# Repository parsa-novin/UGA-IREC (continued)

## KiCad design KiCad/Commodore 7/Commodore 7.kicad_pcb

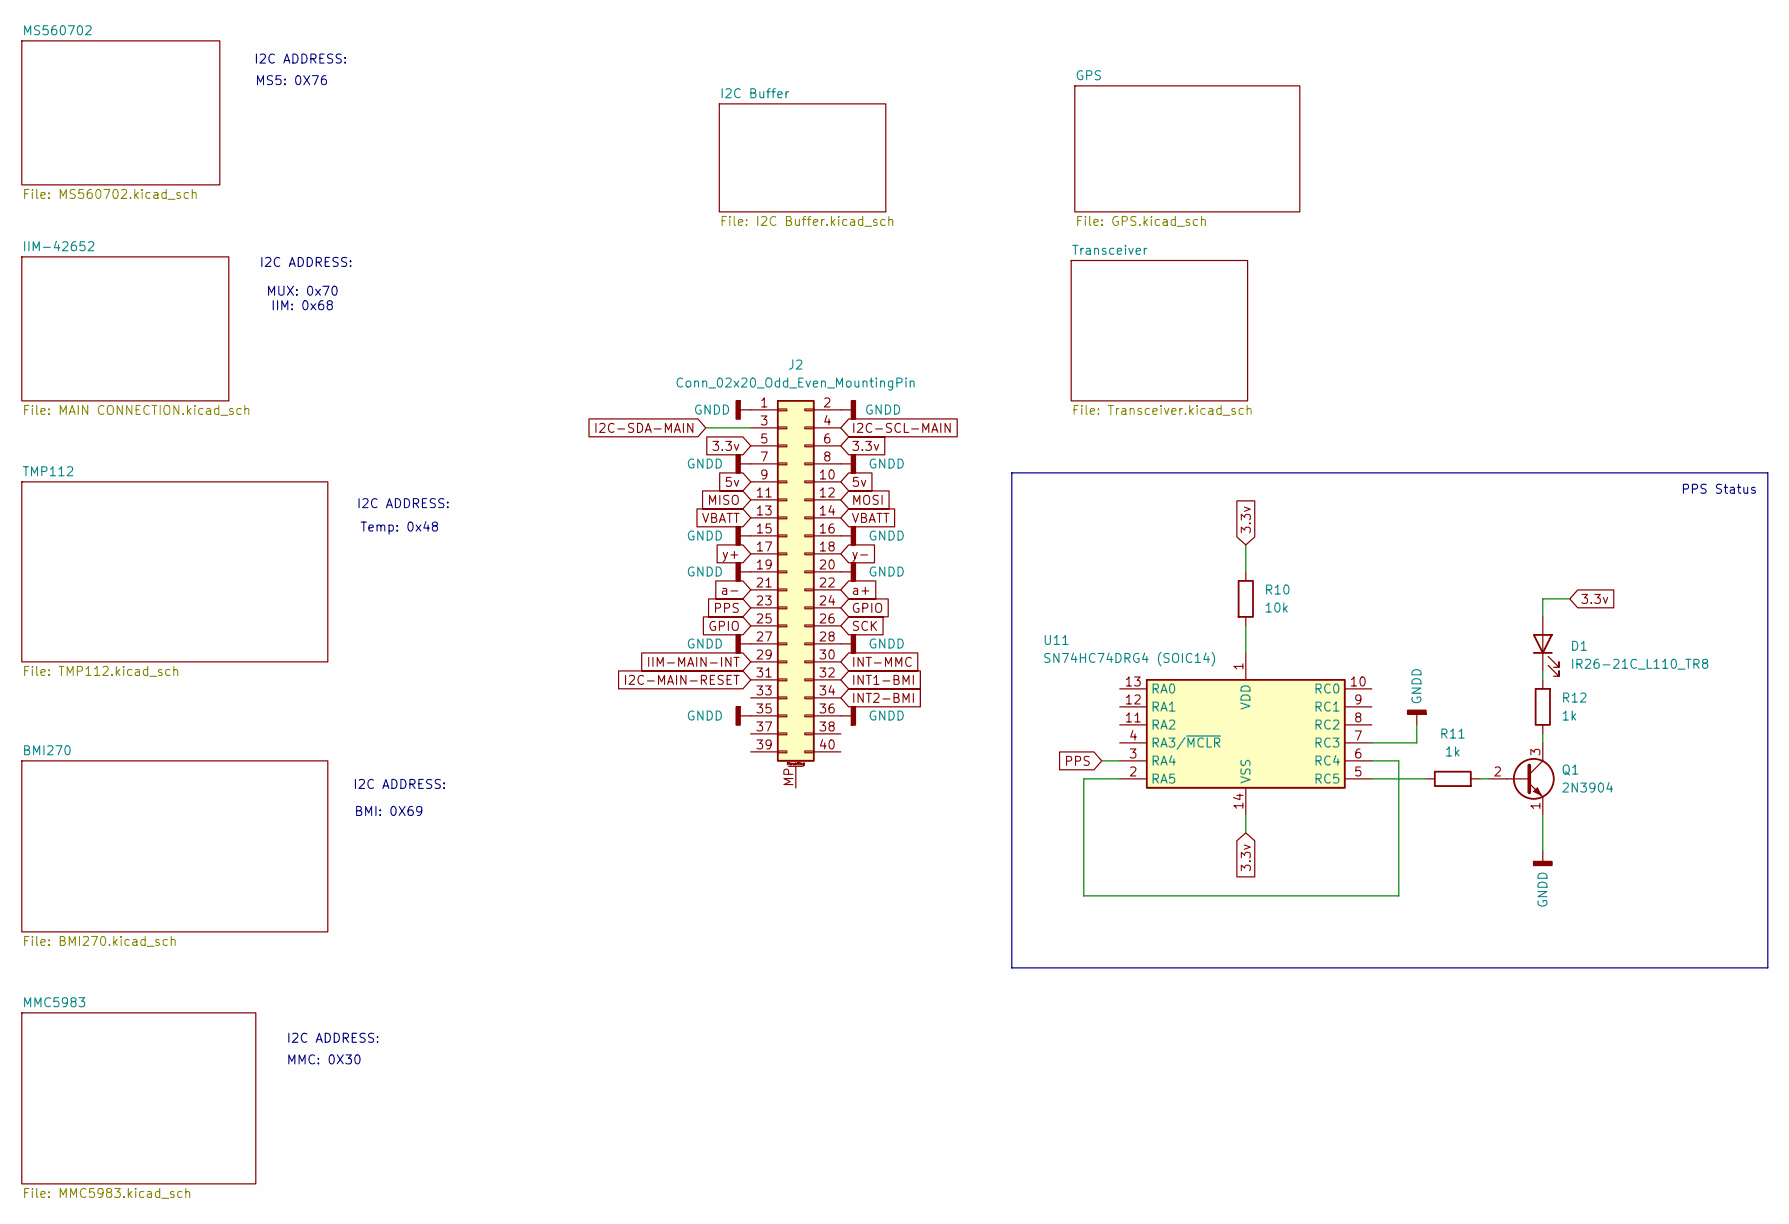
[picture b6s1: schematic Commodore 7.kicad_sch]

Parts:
D1: IR26-21C_L110_TR8; LED_1206_3216Metric
J2: Conn_02x20_Odd_Even_MountingPin; PinHeader_2x20_P2.54mm_Vertical
Q1: 2N3904; TO-92_Inline
R10: 10k; R_1206_3216Metric
R11, R12: 1k; R_1206_3216Metric
U11: SN74HC74DRG4 (SOIC14); SOIC-14_3.9x8.7mm_P1.27mm

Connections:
3.3v: D1.2 (A), J2.5, J2.6, R10.1, U11.14 (VSS); also elsewhere on the board
5v: J2.9, J2.10
GNDD: J2.1, J2.2, J2.7, J2.8, J2.15, J2.16, J2.19, J2.20, J2.27, J2.28, J2.35, J2.36, Q1.1 (E), U11.7 (RC3); also elsewhere on the board
GPIO: J2.24, J2.25; also elsewhere on the board
I2C-MAIN-RESET: J2.31; also elsewhere on the board
I2C-SCL-MAIN: J2.4; also elsewhere on the board
I2C-SDA-MAIN: J2.3; also elsewhere on the board
IIM-MAIN-INT: J2.29; also elsewhere on the board
INT1-BMI: J2.32; also elsewhere on the board
INT2-BMI: J2.34; also elsewhere on the board
INT-MMC: J2.30; also elsewhere on the board
MISO: J2.11
MOSI: J2.12
unnamed: D1.1 (K), R12.2
unnamed: Q1.2 (B), R11.2
unnamed: Q1.3 (C), R12.1
unnamed: U11.2 (RA5), U11.6 (RC4)
unnamed: R11.1, U11.5 (RC5)
unnamed: R10.2, U11.1 (VDD)
PPS: J2.23, U11.3 (RA4); also elsewhere on the board
SCK: J2.26
VBATT: J2.13, J2.14
a+: J2.22; also elsewhere on the board
a-: J2.21; also elsewhere on the board
y+: J2.17; also elsewhere on the board
y-: J2.18; also elsewhere on the board

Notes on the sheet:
I2C ADDRESS:
PPS Status
MUX: 0x70 IIM: 0x68
BMI: 0X69
I2C ADDRESS:
MMC: 0X30
MS5: 0X76
Temp: 0x48

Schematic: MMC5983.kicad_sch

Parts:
C4: 10uF; CAP_CC0805_YAG
C5: 1uF; YAG_CC0603_YAG
U4: MMC5983MA-Magnetomer; PQFN50P300X300X100-16N; PARTREV A

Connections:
3.3v: C5.1, U4.2 (VDD), U4.4 (~SPI_CS), U4.13 (VDDIO); also elsewhere on the board
GNDD: C4.2, C5.2, U4.9 (GND), U4.11 (GND__1); also elsewhere on the board
I2C-SCL-MAIN: U4.1 (SCL/SPI_SCK); also elsewhere on the board
I2C-SDA-MAIN: U4.16 (SDA/SPI_SDI); also elsewhere on the board
INT-MMC: U4.15 (INT); also elsewhere on the board
unnamed: C4.1, U4.10 (CAP)

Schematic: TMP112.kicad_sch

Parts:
C1: 10nF; CAPC17595_87N_KEM
U1: TMP112AIDRLR-Temperature; SOT50P160X60-6N

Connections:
GNDD: C1.2, U1.2 (GND), U1.3 (ALERT), U1.4 (ADD0); also elsewhere on the board
I2C-SCL-MAIN: U1.1 (SCL); also elsewhere on the board
I2C-SDA-MAIN: U1.6 (SDA); also elsewhere on the board
unnamed: C1.1, U1.5 (V+)

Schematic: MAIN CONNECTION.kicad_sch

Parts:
C12, C13: 2.2uf; CAP_CC0805_YAG
C14, C15: .1uf; CC0603N_YAG
C16, C17: 10nF; CAPC17595_87N_KEM
R1, R2, R3, R4: 4.7k; YAG_R0402_YAG
R19, R20, R21, R23, R27, R28: 2.7K; RES0805_CRG_TYCO_TYC
U8: IIM-42652 - Main Accelerometer 2; Bosch_LGA-14_3x2.5mm_P0.5mm
U9: IIM-42652 Main Accelerometer; Bosch_LGA-14_3x2.5mm_P0.5mm
U10: TCA9543APWR; SOP65P640X120-14N

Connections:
3.3v: C12.1, C13.1, C14.1, C15.1, C16.1, C17.1, R1.2, R2.2, R3.2, R4.2, R19.2, R20.2, R21.2, R23.2, R27.2, R28.2, U8.5 (VDDIO), U8.8 (VDD), U8.12 (AP_CS), U9.5 (VDDIO), U9.8 (VDD), U9.12 (AP_CS), U10.14 (VCC); also elsewhere on the board
GNDD: C12.2, C13.2, C14.2, C15.2, C16.2, C17.2, U8.1 (AP_SDO/AP_AD0), U8.6 (GND), U8.7 (GND), U8.9 (INT2/FSYNC/CLKIN), U9.1 (AP_SDO/AP_AD0), U9.6 (GND), U9.7 (GND), U9.9 (INT2/FSYNC/CLKIN), U10.1 (AO), U10.2 (A1), U10.7 (GND); also elsewhere on the board
I2C-MAIN-RESET: R3.1, U10.3 (RESET); also elsewhere on the board
I2C-SCL-MAIN: R2.1, U10.12 (SCL); also elsewhere on the board
I2C-SDA-MAIN: R1.1, U10.13 (SDA); also elsewhere on the board
IIM-MAIN-INT: R4.1, U10.11 (INT); also elsewhere on the board
INT-IIM1: R27.1, U9.4 (INT1/INT), U10.4 (INTO)
INT-IIM2: R28.1, U8.4 (INT1/INT), U10.8 (INT1)
SCL-IIM1: R20.1, U9.13 (AP_SCL/AP_SCLK), U10.6 (SCO)
SCL-IIM2: R19.1, U8.13 (AP_SCL/AP_SCLK), U10.10 (8C1)
SDA-IIM1: R21.1, U9.14 (AP_SDA/AP_SDIO/AP_SDI), U10.5 (SDO)
SDA-IIM2: R23.1, U8.14 (AP_SDA/AP_SDIO/AP_SDI), U10.9 (SD1)

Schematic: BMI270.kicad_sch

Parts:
C2, C3: .1uF; CC0603N_YAG
R6: 2.7K; RES0805_CRG_TYCO_TYC
R8: 2.7K; R_1206_3216Metric
U3: BMI270 - Secondary Accelerometer; XDCR_BMI270

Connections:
3.3v: C2.1, C3.1, R6.1, R8.1, U3.5 (VDDIO), U3.8 (VDD); also elsewhere on the board
GNDD: C2.2, C3.2, U3.6 (GNDIO), U3.7 (GND), U3.10 (OSCB), U3.11 (OSDO); also elsewhere on the board
I2C-SCL-MAIN: U3.13 (SCX); also elsewhere on the board
I2C-SDA-MAIN: U3.14 (SDX); also elsewhere on the board
INT1-BMI: U3.4 (INT1); also elsewhere on the board
INT2-BMI: U3.9 (INT2); also elsewhere on the board
unnamed: R8.2, U3.12 (CSB)
unnamed: R6.2, U3.1 (SDO)

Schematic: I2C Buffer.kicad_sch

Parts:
R9: RC0402FR-0710KL; YAG_R0402_YAG; PARTREV V.12
U6: TCA9509DGKR; DGK8

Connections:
3.3v: R9.2, U6.1 (VCCA), U6.8 (VCCB); also elsewhere on the board
GNDD: U6.4 (GND); also elsewhere on the board
I2C-SCL-MAIN: U6.2 (SCLA), U6.7 (SCLB); also elsewhere on the board
I2C-SDA-MAIN: U6.3 (SDAA), U6.6 (SDAB); also elsewhere on the board
unnamed: R9.1, U6.5 (EN)

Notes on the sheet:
Connect at diffrent points

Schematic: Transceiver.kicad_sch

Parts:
R5, R7: RC1206FR-0724RL; R_1206_3216Metric
U7: SN65HVD74DR; D8_TEX

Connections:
3.3v: U7.1 (VCC); also elsewhere on the board
GNDD: U7.4 (GND); also elsewhere on the board
R: U7.2 (R); also elsewhere on the board
T: U7.3 (D); also elsewhere on the board
a+: R5.1, U7.8 (A); also elsewhere on the board
a-: R5.2, U7.7 (B); also elsewhere on the board
y+: R7.1, U7.5 (Y); also elsewhere on the board
y-: R7.2, U7.6 (Z); also elsewhere on the board

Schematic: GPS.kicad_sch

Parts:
E1: YG0043AA; XDCR_YG0043AA; PARTREV 1.3
IC1: BGU7004,115; BGU7004115; Manufacturer_Part_Number BGU7004,115; Mouser Part Number 771-BGU7004,115
IC2: LD56020M180R; SOT-23-5; Manufacturer_Part_Number LD56020M180R
L1: 5.6nH; INDC1006X60N
U2: NEO-M9N-00B; XCVR_NEO-M9N-00B; PARTREV R05
U12: RSF-1575.420-24000-3030-TR

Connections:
3.3v: IC2.1 (VIN), IC2.3 (EN), U2.2 (D_SEL), U2.23 (VCC); also elsewhere on the board
GNDD: IC1.1 (GND_1), IC1.2 (GND_2), IC2.2 (GND), U2.10 (GND), U2.12 (GND__1), U2.13 (GND__2), U2.24 (GND__3), U12.1 (gnd), U12.3 (gnd), U12.4 (gnd), U12.6 (gnd); also elsewhere on the board
GPIO: U2.8 (RESET_N); also elsewhere on the board
unnamed: IC1.3 (RF_IN), L1.2
unnamed: IC1.6 (RF_OUT), U2.11 (RF_IN)
unnamed: IC1.4 (VCC), IC2.5 (VOUT)
unnamed: E1.1, U12.2 (2_Rf_in)
unnamed: L1.1, U12.5 (5_Rf_output)
PPS: U2.3 (TIMEPULSE); also elsewhere on the board
R: U2.21 (RXD/SPI_MOSI); also elsewhere on the board
T: U2.20 (TXD/SPI_MISO); also elsewhere on the board

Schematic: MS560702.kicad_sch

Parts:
U5: MS560702BA03-50 - Barometer; SON125P300X500X100-8N

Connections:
3.3v: U5.1 (VDD), U5.2 (PS); also elsewhere on the board
GNDD: U5.3 (GND), U5.4 (~CSB), U5.5 (~CSB__1), U5.6 (SDO); also elsewhere on the board
I2C-SCL-MAIN: U5.8 (SCLK); also elsewhere on the board
I2C-SDA-MAIN: U5.7 (SDI/SDA); also elsewhere on the board

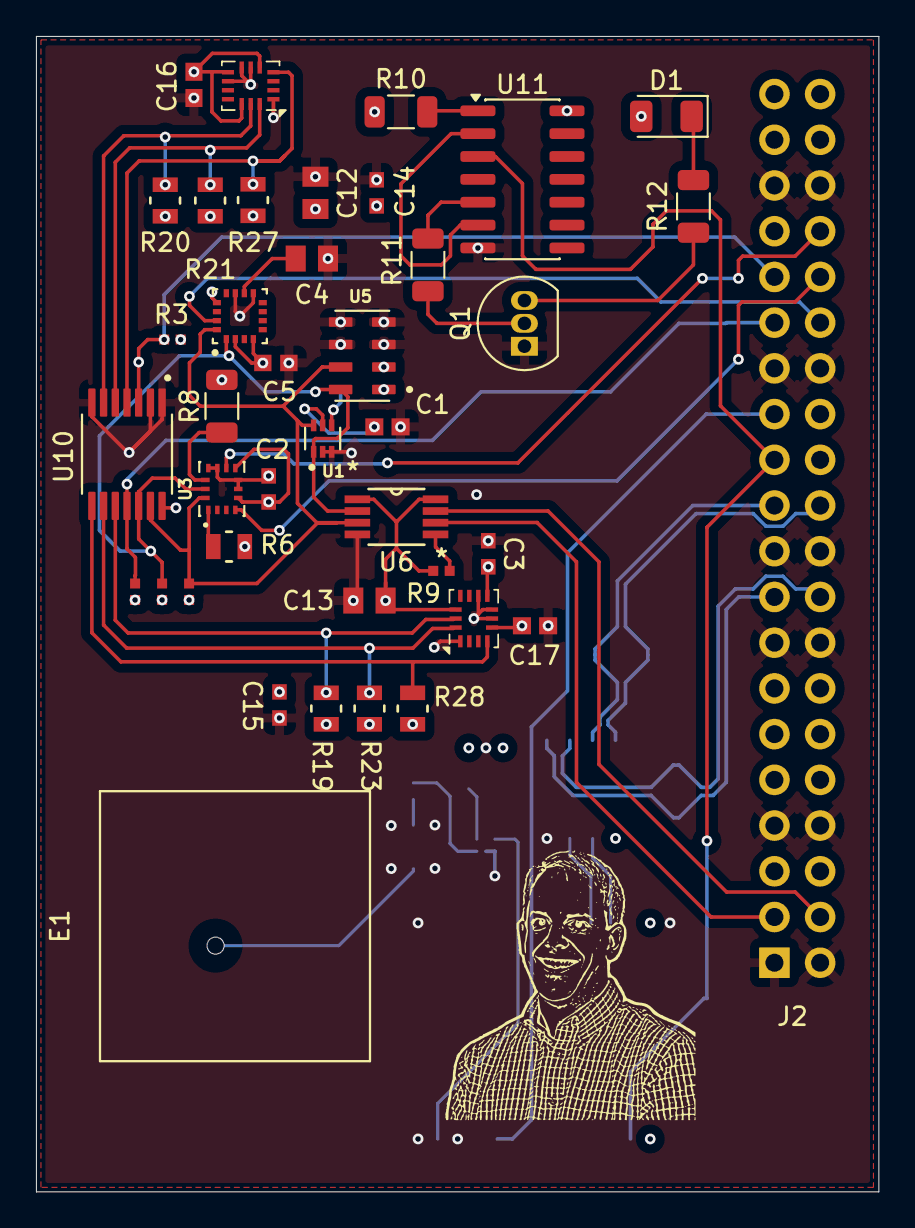
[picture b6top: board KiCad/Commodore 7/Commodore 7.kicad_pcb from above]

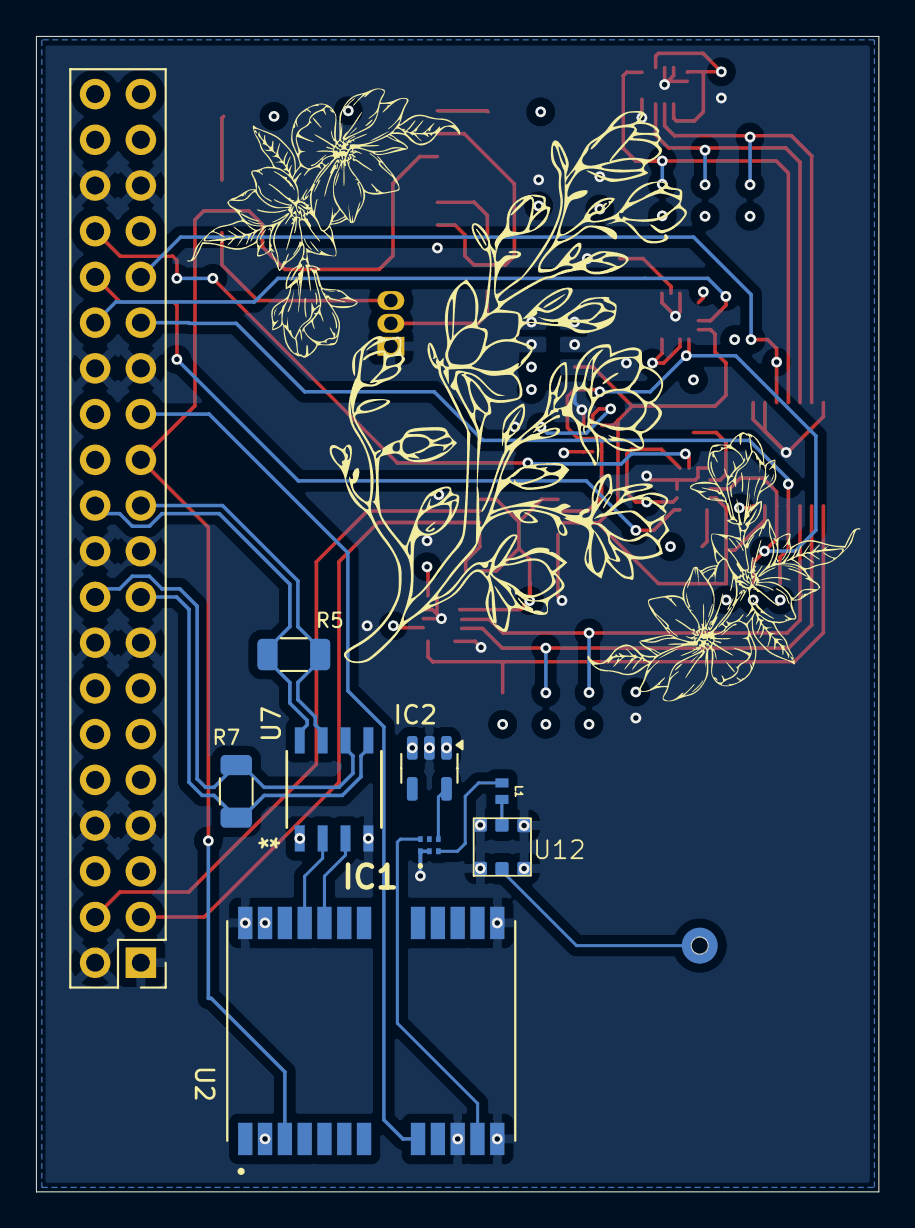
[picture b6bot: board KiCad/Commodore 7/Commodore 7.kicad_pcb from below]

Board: 4 copper layers, 46.8 x 64.2 mm, 48 parts (9 on the bottom side), 41 nets.

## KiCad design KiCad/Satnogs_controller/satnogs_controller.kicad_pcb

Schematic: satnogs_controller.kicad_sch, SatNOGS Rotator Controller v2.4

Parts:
A1, A2: Pololu_Breakout_A4988; Pololu_Breakout-16_15.2x20.3mm
C1, C2, C6, C7, C11, C13: 0.1u; C_0805_2012Metric_Pad1.15x1.40mm_HandSolder
C3, C14, C15: 100u; CP_Elec_6.3x5.3
C4: 100u; CP_Radial_D10.0mm_P5.00mm
C5: 2.2u; C_1210_3225Metric_Pad1.42x2.65mm_HandSolder
C8: 7.5n; C_0805_2012Metric_Pad1.15x1.40mm_HandSolder
C9: 100n; C_0805_2012Metric_Pad1.15x1.40mm_HandSolder
C10: 10p; C_0805_2012Metric_Pad1.15x1.40mm_HandSolder
C12: 47u; C_1210_3225Metric_Pad1.42x2.65mm_HandSolder
D1: D_TVS; D_SMC_Handsoldering
D2, D4: D_Schottky; D_SMC_Handsoldering
D3: D_TVS_x2_AAC; SOT-23_Handsoldering
F1: FUSE; Fuse_1206_3216Metric_Pad1.42x1.75mm_HandSolder
FB1: FILTER - POWER; R_0805_2012Metric_Pad1.15x1.40mm_HandSolder
FB2: FILTER; R_0805_2012Metric_Pad1.15x1.40mm_HandSolder
J1: Conn_01x06_Pin; JST_XA_B06B-XASK-1_1x06_P2.50mm_Vertical
JP1, JP2, JP3, JP4, JP5, JP6, JP7, JP8: Jumper_NO_Small; R_0805_2012Metric_Pad1.15x1.40mm_HandSolder
L1: 27u; L_Bourns_SRR1210A
P1: ISP; PinHeader_2x03_P2.54mm_Vertical
P2: INPUT; PinHeader_2x05_P2.54mm_Vertical
P3: GND-PAD; MountingHole_2.2mm_M2_DIN965_Pad
P4: I2C; PinHeader_2x04_P2.54mm_Vertical
P5: End-Stops; PinHeader_2x03_P2.54mm_Vertical
P6: DEV-PINS; PinHeader_2x04_P2.54mm_Vertical
P7, P8: Motor; TerminalBlock_Phoenix_MKDS-1,5-4_1x04_P5.00mm_Horizontal
R1, R2: 10k; R_0805_2012Metric_Pad1.15x1.40mm_HandSolder
R3, R4: 10; R_0805_2012Metric_Pad1.15x1.40mm_HandSolder
R5: 120; R_0805_2012Metric_Pad1.15x1.40mm_HandSolder
R6: 221k; R_0805_2012Metric_Pad1.15x1.40mm_HandSolder
R7, R8, R13, R15, R16, R17: 4.7k; R_0805_2012Metric_Pad1.15x1.40mm_HandSolder
R9: 26.7k; R_0805_2012Metric_Pad1.15x1.40mm_HandSolder
R10, R14: 200; R_0805_2012Metric_Pad1.15x1.40mm_HandSolder
R11: 147k; R_0805_2012Metric_Pad1.15x1.40mm_HandSolder
R12: 10.5k; R_0805_2012Metric_Pad1.15x1.40mm_HandSolder
R18, R19: 100k; R_0805_2012Metric_Pad1.15x1.40mm_HandSolder
U1: SN65HVD485EDR; SOIC-8_3.9x4.9mm_P1.27mm
U2: Arduino_Pro_Mini_328
U3: TPS54360DDA; Texas_HSOP-8-1EP_3.9x4.9mm_P1.27mm_ThermalVias
U4: TC74; SOT-23-5_HandSoldering
U5: PCA9540B; TSSOP-8_3x3mm_P0.65mm
U6: Pololu_Dual_MC33926

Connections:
+5V: A1.2 (VDD), A2.2 (VDD), C1.1, C6.1, C11.2, JP3.2, JP4.2, JP5.2, JP6.1, JP7.1, JP8.1, P1.2, P4.2, P4.6, P5.5, P5.6, P6.2, P6.6, R2.1, R7.1, R8.1, R13.1, R15.1, R16.1, R17.1, U1.8 (VDD), U2.25 (VCC), U4.3 (VDD), U5.3 (VDD), U6.3 (VDD)
+12V: A1.8 (VMOT), A2.8 (VMOT), C12.1, C14.1, C15.1, FB2.2, J1.2, L1.2, R11.1, U6.26 (VMOT)
/1AM1: A1.4 (1A), P7.2
/1AM2: A2.4 (1A), P8.2
/1BM1: A1.3 (1B), P7.1
/1BM2: A2.3 (1B), P8.1
/2AM1: A1.5 (2A), P7.3
/2AM2: A2.5 (2A), P8.3
/2BM1: A1.6 (2B), P7.4
/2BM2: A2.6 (2B), P8.4
/A: D3.2 (A2), JP1.1, P2.8, R4.1, R5.2
/A2: J1.3, P6.3, U2.21 (PC2/A2)
/A3: P6.1, U2.22 (PC3/A3)
/B: D3.1 (A1), JP2.1, P2.7, R3.2, R5.1
/BOOT: C9.1, U3.1 (BOOT)
/COMP: C10.1, R9.1, U3.6 (COMP)
/DTR: C2.2, P2.9
/EN: A1.9 (~ENABLE), A2.9 (~ENABLE), U2.11 (PB0/8), U6.10 (EN)
/FB: R11.2, R12.1, U3.5 (FB)
/M1D1: U6.7 (M1D1), U6.24 (GND)
/M1D2: U6.6 (M1D2), U6.25 (VDD-OUT)
/M1FB: U2.20 (PC1/A1), U6.9 (M1FB)
/M1IN1: A1.15 (STEP), U2.13 (PB2/10), U6.5 (M1IN1)
/M1IN2: A1.16 (DIR), U2.12 (PB1/9), U6.4 (M1IN2)
/M1RST: A1.13 (~RESET), A1.14 (~SLEEP)
/M1SF: U2.10 (PD7/7), U6.8 (M1SF)
/M2D1: U6.16 (M2D1), U6.19 (GND)
/M2D2: U6.15 (M2D2), U6.20 (VDD-OUT)
/M2FB: U2.19 (PC0/A0), U6.18 (M2FB)
/M2IN1: A2.15 (STEP), J1.5, P1.4, U2.14 (PB3/11), U6.14 (M2IN1)
/M2IN2: A2.16 (DIR), U2.6 (PD3/3), U6.13 (M2IN2)
/M2RST: A2.13 (~RESET), A2.14 (~SLEEP)
/M2SF: U2.9 (PD6/6), U6.17 (M2SF)
/MS1M1: A1.10 (MS1), JP3.1, R18.1
/MS1M2: A2.10 (MS1), JP6.2, R19.1
/MS2M1: A1.11 (MS2), JP4.1
/MS2M2: A2.11 (MS2), JP7.2
/MS3M1: A1.12 (MS3), JP5.1
/MS3M2: A2.12 (MS3), JP8.2
/PB4: J1.6, P1.1, P6.8, U2.15 (PB4/12)
/PB5: J1.4, P1.3, P6.5, U2.16 (PB5/13)
/RST: C2.1, P1.5, U2.26 (PC6/RST)
/RTS: R1.1, U1.2 (~RE), U1.3 (DE), U2.5 (PD2/2)
/RT/CLK: R6.1, U3.4 (RT/CLK)
/RX: JP2.2, R2.2, U1.1 (R), U2.2 (PD0/RX)
/SCL: R8.2, U2.24 (PC5/A5), U5.1 (SCL)
/SCL0: P4.5, R15.2, U5.5 (SC0)
/SCL1: P4.1, R17.2, U4.4 (SCLK), U5.8 (SC1)
/SDA: R7.2, U2.23 (PC4/A4), U5.2 (SDA)
/SDA0: P4.7, R13.2, U5.4 (SD0)
/SDA1: P4.3, R16.2, U4.5 (SDA), U5.7 (SD1)
/SW: C9.2, D4.1 (K), L1.1, U3.8 (SW)
/SW1: C7.2, R10.1, U2.8 (PD5/5)
/SW2: C13.1, R14.2, U2.7 (PD4/4)
/SW_VIN: C4.1, C5.1, D2.1 (K), F1.1, U3.2 (VIN)
/TX: JP1.2, U1.4 (D), U2.1 (PD1/TX)
/VIN: D1.1 (A1), FB1.2, P2.1, P2.2
GND: A1.1 (GND), A1.7 (GND), A2.1 (GND), A2.7 (GND), C1.2, C3.2, C4.2, C5.2, C6.2, C7.1, C8.2, C10.2, C11.1, C12.2, C13.2, C14.2, C15.2, D1.2 (A2), D2.2 (A), D3.3 (common), D4.2 (A), J1.1, P1.6, P2.3, P2.4, P2.5, P2.6, P2.10, P3.1, P4.4, P4.8, P5.3, P5.4, P6.4, P6.7, R1.2, R6.2, R12.2, R18.2, R19.2, U1.5 (GND), U2.4 (GND), U2.27 (GND), U3.7 (GND), U3.9 (GNDPAD), U4.2 (GND), U5.6 (VSS), U6.2 (GND), U6.27 (GND)
unnamed: C8.1, R9.2
unnamed: F1.2, FB1.1
unnamed: P5.1, R10.2
unnamed: P5.2, R14.1
unnamed: R4.2, U1.6 (A)
unnamed: R3.1, U1.7 (B)
unnamed: C3.1, FB2.1, U2.28 (RAW)

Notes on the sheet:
RS-485 and power supply have Common GND. RS-485 requires ground wire to equalize node voltage differences.
Regulator in pro-mini, is MIC5205: 5V@150mA with reverse-current protection Filter switching regulator for 5V LDO. Cut 440kHz of switching regulator.
Solder to have UART as communication
Debouncing filter for the mechanichal end-stops. http://wot.lv/combating-endstop-noise-on-a-reprap.html
For distance problems, use P82B715 I2C extender (for now we don't need)
Power Supply Module
D2 is for inverse voltage protection
Note for microstepping MS1 MS2 MS3 Microstep Low Low Low Full High Low Low Half Low High Low Quarter High High Low Eighth High High High Sixteenth
Vout: 12V@3A
Always follow NEC guidelines for applying low-voltage fuses. Generally, the MINIMUM fuse size should be based on 125% of the circuits full load current. Time-delay fuses should be used for inductive loads.
The characteristic impedance of UTP CAT5, CAT6 is around 100ohm. With 120ohm termination in both sides, may get good results with these cables (Must be within 20%).
GND Pad for box shielding
DC Motors
D4 is optional, for transient voltage suppressor
M1IN1->STEPM1->D6 M1IN2->DIRM1->D5 M2IN1->STEPM2->D10 M2IN2->DIRM2->D9 SLEW/INV default state: GND
VIN: 20 - 60V
Stepper Motors

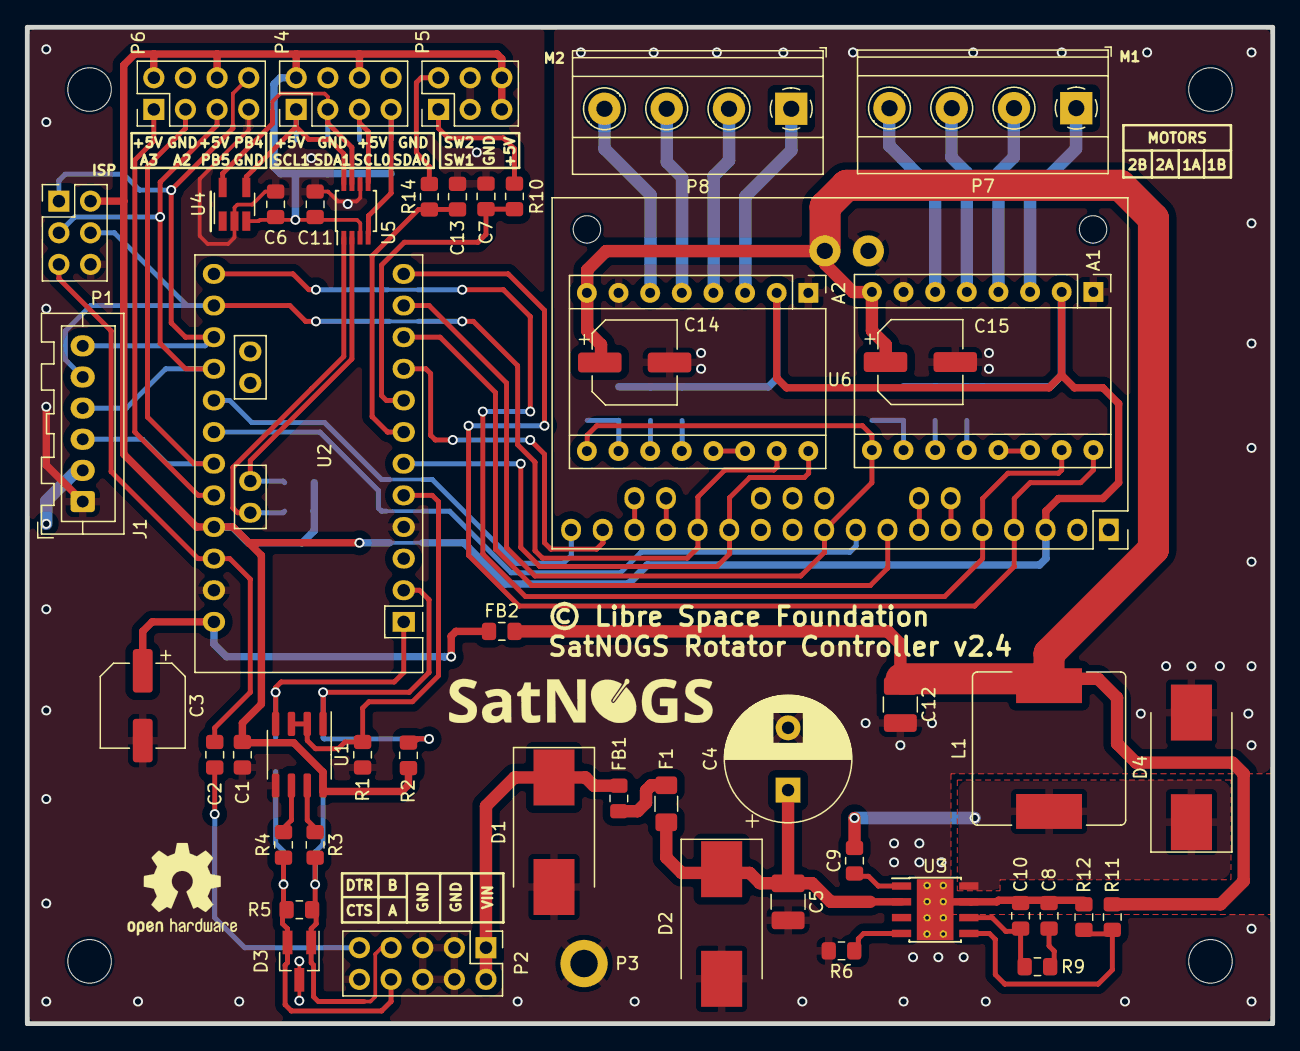
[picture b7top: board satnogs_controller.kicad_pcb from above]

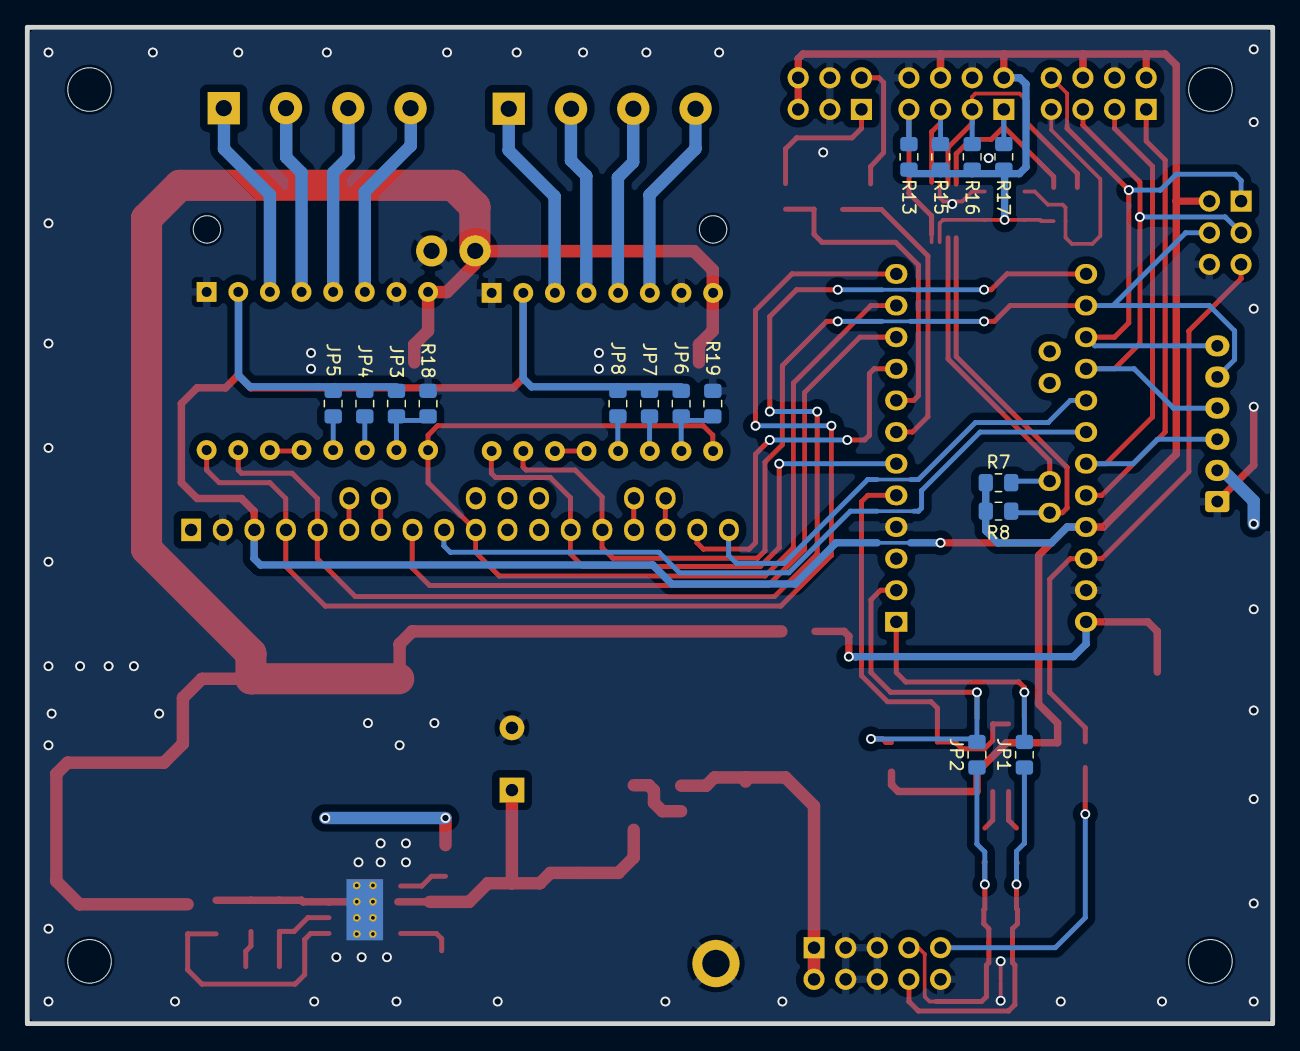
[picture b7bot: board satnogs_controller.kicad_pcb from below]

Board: 2 copper layers, 100.0 x 80.0 mm, 68 parts (16 on the bottom side), 65 nets.

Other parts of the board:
Board: EuroBoard_halb_Type-I_100mmX80mm_holes

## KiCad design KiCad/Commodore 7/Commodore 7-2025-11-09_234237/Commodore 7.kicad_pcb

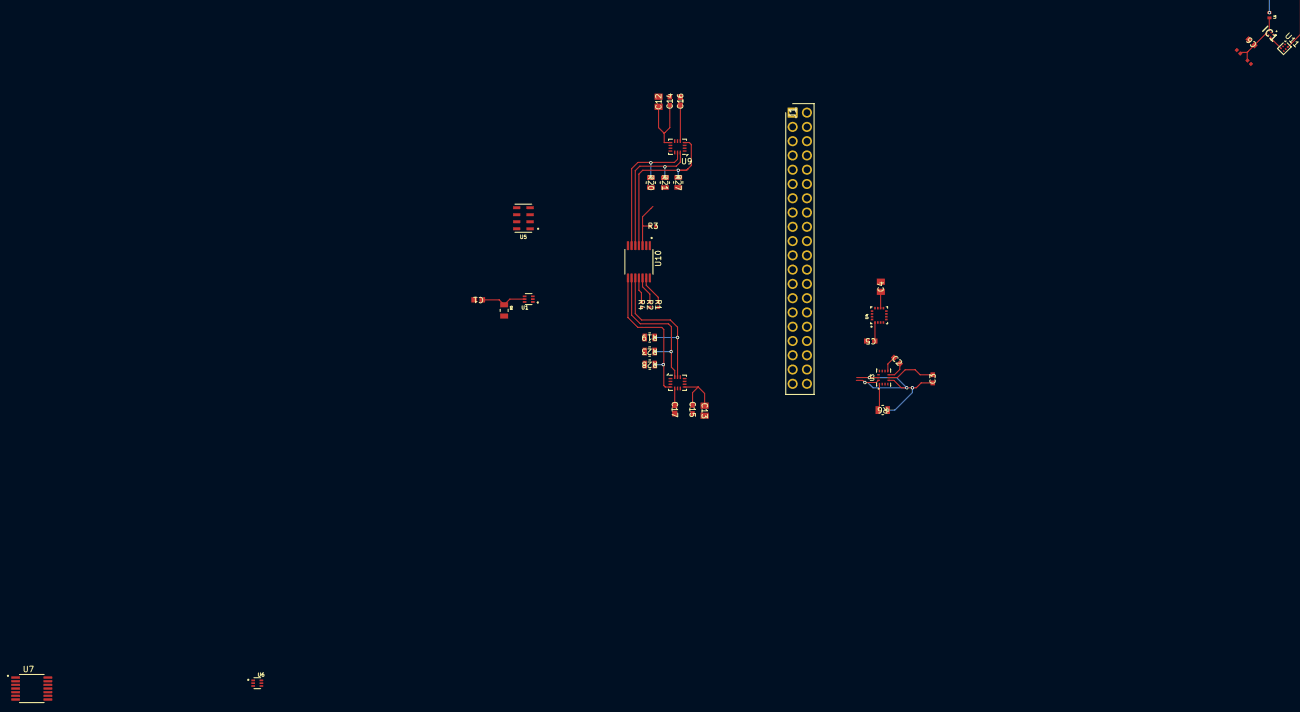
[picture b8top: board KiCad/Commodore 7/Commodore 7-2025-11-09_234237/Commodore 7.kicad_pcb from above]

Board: 2 copper layers, 41 parts (1 on the bottom side), 23 nets.

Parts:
C1, C16, C17: 10nF; CAPC17595_87N_KEM
C2, C3: .1uF; CC0603N_YAG
C4: 10uF; CAP_CC0805_YAG
C5: 1uF; YAG_CC0603_YAG
C6: 1nF; CC0603N_YAG
C12, C13: 2.2uf; CAP_CC0805_YAG
C14, C15: .1uf; CC0603N_YAG
E1: YG0043AA; XDCR_YG0043AA
IC1: BGU7004,115; BGU7004115
J1: M20-6112045; RHDR40W69P254_2X20_5146X500X1105P
L1: 5.6nH; INDC1006X60N
R1, R2, R3, R4: 4.7k; YAG_R0402_YAG
R5: 5K; RESC2012X50N
R6, R19, R20, R21, R23, R27, R28: 2.7K; RES0805_CRG_TYCO_TYC
R7, R8: 50 Ohm; RESC1005X35N
U1: TMP112AIDRLR-Temperature; SOT50P160X60-6N
U2: NEO-M9N-00B; XCVR_NEO-M9N-00B
U3: BMI270 - Secondary Accelerometer; XDCR_BMI270
U4: MMC5983MA-Magnetomer; PQFN50P300X300X100-16N
U5: MS560702BA03-50 - Barometer; SON125P300X500X100-8N
U6: TCA9509DGKR; SOT50P160X60-6N
U7: SN65HVD74DR; SOP65P640X120-14N
U8: IIM-42652 - Main Accelerometer 2; Bosch_LGA-14_3x2.5mm_P0.5mm
U9: IIM-42652 Main Accelerometer; Bosch_LGA-14_3x2.5mm_P0.5mm
U10: TCA9543APWR; SOP65P640X120-14N
U11: SOT-886

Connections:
3.3v: C2.1, C3.1, C5.1, C12.1, C13.1, C14.1, C15.1, C16.1, C17.1, R1.2, R2.2, R3.2, R4.2, R6.1, R7.1, R19.2, R20.2, R21.2, R23.2, R27.2, R28.2, U1.1 (SCL), U1.6 (SDA), U2.2 (D_SEL), U2.23 (VCC), U3.5 (VDDIO), U3.8 (VDD), U3.12 (CSB), U3.13 (SCX), U3.14 (SDX), U4.1 (SCL/SPI_SCK), U4.2 (VDD), U4.4 (~SPI_CS), U4.13 (VDDIO), U4.16 (SDA/SPI_SDI), U5.1 (VDD), U5.2 (PS), U5.7 (SDI/SDA), U5.8 (SCLK), U8.5 (VDDIO), U8.8 (VDD), U8.12 (AP_CS), U9.5 (VDDIO), U9.8 (VDD), U9.12 (AP_CS), U10.14 (VCC), U11.4 (Vcc)
+3.3V: U6.1 (VCCA), U7.1 (VCC)
GNDA: C1.2, C5.2, C6.2, C12.2, C13.2, C14.2, C15.2, C16.2, C17.2, IC1.1 (GND_1), IC1.2 (GND_2), R8.2, U2.10 (GND), U2.12 (GND__1), U2.13 (GND__2), U2.24 (GND__3), U11.1 (GND), U11.2 (GND)
GNDD: C2.2, C3.2, C4.2, U1.2 (GND), U1.3 (ALERT), U1.4 (ADD0), U3.6 (GNDIO), U3.7 (GND), U3.10 (OSCB), U3.11 (OSDO), U4.9 (GND), U4.11 (GND__1), U5.3 (GND), U5.4 (~CSB), U5.5 (~CSB__1), U5.6 (SDO), U6.4 (GND), U7.4 (GND), U8.1 (AP_SDO/AP_AD0), U8.6 (GND), U8.7 (GND), U8.9 (INT2/FSYNC/CLKIN), U9.1 (AP_SDO/AP_AD0), U9.6 (GND), U9.7 (GND), U9.9 (INT2/FSYNC/CLKIN), U10.1 (AO), U10.2 (A1), U10.7 (GND)
I2C-MAIN-RESET: R3.1, U10.3 (RESET)
I2C-SLC-MAIN: R2.1, U10.12 (SCL)
I2C_SDA: U6.3 (SDAA), U6.6 (SDAB)
IIM-MAIN-INT: R4.1, U10.11 (INT)
IIM-SDA-MAIN: R1.1, U10.13 (SDA)
INT-IIM1: R27.1, U9.4 (INT1/INT), U10.4 (INTO)
INT-IIM2: R28.1, U8.4 (INT1/INT), U10.8 (INT1)
unnamed: E1.1, L1.1
unnamed: IC1.3 (RF_IN), L1.2
unnamed: IC1.6 (RF_OUT), U11.3 (RF_IN)
unnamed: C6.1, IC1.4 (VCC), R7.2, R8.1
unnamed: C1.1, R5.1, U1.5 (V+)
unnamed: R6.2, U3.1 (SDO)
unnamed: C4.1, U4.10 (CAP)
unnamed: U2.11 (RF_IN), U11.6 (RF_OUT)
SCL-IIM1: R20.1, U9.13 (AP_SCL/AP_SCLK), U10.6 (SCO)
SCL-IIM2: R19.1, U8.13 (AP_SCL/AP_SCLK), U10.10 (8C1)
SDA-IIM1: R21.1, U9.14 (AP_SDA/AP_SDIO/AP_SDI), U10.5 (SDO)
SDA-IIM2: R23.1, U8.14 (AP_SDA/AP_SDIO/AP_SDI), U10.9 (SD1)

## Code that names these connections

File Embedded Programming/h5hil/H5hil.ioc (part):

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Mcu.Name=STM32H562RITx
Mcu.Package=LQFP64
Mcu.UserName=STM32H562RITx
PA0.Mode=Asynchronous
PA0.Signal=UART4_TX
PA1.Mode=Asynchronous
PA1.Signal=UART4_RX
PA10.Mode=Asynchronous
PA10.Signal=USART1_RX
PA2.Mode=Asynchronous
PA2.Signal=USART2_TX
PA3.Mode=Asynchronous
PA3.Signal=USART2_RX
PA4.GPIOParameters=GPIO_PuPd,GPIO_ModeDefaultEXTI
PA4.GPIO_ModeDefaultEXTI=GPIO_MODE_IT_RISING_FALLING
PA4.GPIO_PuPd=GPIO_PULLDOWN
PA4.Signal=GPXTI4
PA6.GPIOParameters=GPIO_PuPd,GPIO_ModeDefaultEXTI
PA6.GPIO_ModeDefaultEXTI=GPIO_MODE_IT_RISING_FALLING
PA6.GPIO_PuPd=GPIO_PULLDOWN
PA6.Signal=GPXTI6
PA7.GPIOParameters=GPIO_PuPd,GPIO_ModeDefaultEXTI
PA7.GPIO_ModeDefaultEXTI=GPIO_MODE_IT_RISING_FALLING
PA7.GPIO_PuPd=GPIO_PULLDOWN
PA7.Signal=GPXTI7
PA9.Mode=Asynchronous
PA9.Signal=USART1_TX
PB1.Signal=S_TIM3_CH4
PB10.Mode=Full_Duplex_Master
PB10.Signal=SPI2_SCK
PB12.Mode=NSS_Signal_Hard_Output
PB12.Signal=SPI2_NSS
PB13.Mode=Asynchronous
PB13.Signal=UART5_TX
PB14.Mode=Full_Duplex_Master
PB14.Signal=SPI2_MISO
PB15.Mode=Full_Duplex_Master
PB15.Signal=SPI2_MOSI
PB5.Mode=Asynchronous
PB5.Signal=UART5_RX
PC10.Mode=SD_4_bits_Wide_bus
PC10.Signal=SDMMC1_D2
PC11.Mode=SD_4_bits_Wide_bus
PC11.Signal=SDMMC1_D3
PC12.Mode=SD_4_bits_Wide_bus
PC12.Signal=SDMMC1_CK
PC5.Signal=GPXTI5
PC8.Mode=SD_4_bits_Wide_bus
PC8.Signal=SDMMC1_D0
PC9.Mode=SD_4_bits_Wide_bus
PC9.Signal=SDMMC1_D1
PD2.Mode=SD_4_bits_Wide_bus
PD2.Signal=SDMMC1_CMD
RCC.HSE_VALUE=25000000
RCC.SYSCLKFreq_VALUE=250000000
RCC.SYSCLKSource=RCC_SYSCLKSOURCE_PLLCLK
board=custom

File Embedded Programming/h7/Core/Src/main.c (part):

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  *
  * ADV7280 video decoder
  * ----------------------
  * I2C3 (PC0 = SCL, PC1 = SDA, AF4), address 0x20.
  * DCMI 8-bit BT.656 embedded-sync: D0–D7 on PC6/PC7/PB13/PC9/PC11/PD3/PB8/PB9,
  * PIXCLK on PA6.  Initialised for NTSC composite (CVBS on AIN1) at startup.
  * Data capture is not started; DMA must be configured before calling
  * HAL_DCMI_Start_DMA() when image capture is required.
  *
  * ADV7280 control signals
  * -----------------------
  *   PA8  (ADV_INTR)    — active-low interrupt input (open-drain, pull-up fitted)
  *   PC14 (ADV_PWRDWN)  — active-low power-down; driven HIGH on boot
  *   PC3  (CAM_MUX_SEL) — external mux select; LOW = camera 0 (default)
  *
  * SPI2 slave interface (8-bit frames, mode 0, MSB first):
  *   'R' (0x52) — Start recording
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  *
  * INA219 wiring
  * -------------
  * I2C1 (PB6 = SCL, PB7 = SDA), address 0x45 (A1=VS, A0=GND).
  * See ina219.h for shunt resistor and max-current configuration.
  ******************************************************************************
  * @attention
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/* Private variables ---------------------------------------------------------*/
DCMI_HandleTypeDef hdcmi;
I2C_HandleTypeDef  hi2c1;
I2C_HandleTypeDef  hi2c3;   /* ADV7280 video decoder (PC0=SCL, PC1=SDA) */
SPI_HandleTypeDef  hspi2;
UART_HandleTypeDef huart4;

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/**
  * @brief I2C3 Initialisation Function — ADV7280 video decoder bus.
  *
  * Operates at 400 kHz (Fast Mode) on PC0 (SCL) and PC1 (SDA).
  * Timing register is identical to I2C1 since both share the same
  * APB1 clock domain at 16 MHz.
  *
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  * Configured for 8-bit embedded-sync (BT.656) mode with a rising-edge
  * pixel clock.  The ADV7280 outputs standard NTSC at 27 MHz on the
  * parallel data bus; HSYNC and VSYNC are embedded in the data stream
  * (SAV/EAV codes) so no separate sync GPIO pins are required.
  *
  * NOTE: stm32h7xx_hal_dcmi.h and stm32h7xx_hal_dcmi.c must be copied
  * from the STM32Cube_FW_H7 package into the Drivers/STM32H7xx_HAL_Driver
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  * @brief ADC1 Initialisation Function
  *
  * Configured for single-channel differential measurement on INN5/INP5
  * (PB0/PB1).  Not used by the current firmware but left initialised so
  * the peripheral is ready if needed.
  *
  * @retval None
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}

/**
  * @brief GPIO Initialisation Function
  * @retval None
  */
static void MX_GPIO_Init(void)
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    __HAL_RCC_GPIOC_CLK_ENABLE();

    /*
     * ADV_PWRDWN (PC14) — active-low power-down for the ADV7280.
     * Pre-write HIGH before configuring the pin so the chip is never
     * inadvertently powered down on the first clock cycle after init.
     */
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    HAL_GPIO_Init(ADV_PWRDWN_GPIO_Port, &GPIO_InitStruct);

    /*
     * CAM_MUX_SEL (PC3) — external camera multiplexer select.
     * LOW selects camera 0 (default).  Drive before configuring the pin
     * for the same reason as PWRDWN above.
     */
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    GPIO_InitStruct.Speed = GPIO_SPEED_FREQ_LOW;
    HAL_GPIO_Init(CAM_MUX_SEL_GPIO_Port, &GPIO_InitStruct);

    /* ADV_INTR (PA8) — active-low interrupt from the ADV7280.
     * Pull-up because the ADV7280 INTR pin is open-drain. */
    GPIO_InitStruct.Pin   = ADV_INTR_Pin;
    GPIO_InitStruct.Mode  = GPIO_MODE_INPUT;
    GPIO_InitStruct.Pull  = GPIO_PULLUP;
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
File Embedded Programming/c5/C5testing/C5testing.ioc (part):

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Mcu.Name=STM32C051K8Tx
Mcu.Package=LQFP32
Mcu.UserName=STM32C051K8Tx
PA1.GPIOParameters=GPIO_Speed,GPIO_PuPd
PA1.GPIO_PuPd=GPIO_PULLDOWN
PA1.GPIO_Speed=GPIO_SPEED_FREQ_HIGH
PA1.Mode=Full_Duplex_Master
PA1.Signal=SPI1_SCK
PA11\ [PA9].GPIOParameters=GPIO_Speed,GPIO_PuPd
PA11\ [PA9].GPIO_PuPd=GPIO_NOPULL
PA11\ [PA9].GPIO_Speed=GPIO_SPEED_FREQ_HIGH
PA11\ [PA9].Mode=Full_Duplex_Master
PA11\ [PA9].Signal=SPI1_MISO
PA15.GPIOParameters=PinState,GPIO_PuPd
PA15.GPIO_PuPd=GPIO_PULLUP
PA15.PinState=GPIO_PIN_SET
PA15.Signal=GPIO_Output
PA2.GPIOParameters=GPIO_Speed,GPIO_PuPd
PA2.GPIO_PuPd=GPIO_PULLDOWN
PA2.GPIO_Speed=GPIO_SPEED_FREQ_HIGH
PA2.Mode=Full_Duplex_Master
PA2.Signal=SPI1_MOSI
PA4.GPIOParameters=PinState,GPIO_PuPd
PA4.GPIO_PuPd=GPIO_PULLUP
PA4.PinState=GPIO_PIN_SET
PA4.Signal=GPIO_Output
PA6.Mode=Asynchronous
PA6.Signal=USART1_TX
PA7.Mode=Asynchronous
PA7.Signal=USART1_RX
PA8.GPIOParameters=PinState,GPIO_PuPd
PA8.GPIO_PuPd=GPIO_PULLUP
PA8.PinState=GPIO_PIN_SET
PA8.Signal=GPIO_Output
PB0.GPIOParameters=PinState,GPIO_PuPd
PB0.GPIO_PuPd=GPIO_PULLUP
PB0.PinState=GPIO_PIN_SET
PB0.Signal=GPIO_Output
PB4.GPIOParameters=PinState,GPIO_PuPd
PB4.GPIO_PuPd=GPIO_PULLUP
PB4.PinState=GPIO_PIN_SET
PB4.Signal=GPIO_Output
PB5.GPIOParameters=PinState,GPIO_PuPd
PB5.GPIO_PuPd=GPIO_PULLUP
PB5.PinState=GPIO_PIN_SET
PB5.Signal=GPIO_Output
PB8.GPIOParameters=PinState,GPIO_PuPd
PB8.GPIO_PuPd=GPIO_PULLUP
PB8.PinState=GPIO_PIN_SET
PB8.Signal=GPIO_Output
PB9.GPIOParameters=PinState,GPIO_PuPd
PB9.GPIO_PuPd=GPIO_PULLUP
PB9.PinState=GPIO_PIN_SET
PB9.Signal=GPIO_Output
RCC.HSE_VALUE=8000000
RCC.SYSCLKFreq_VALUE=12000000
board=custom

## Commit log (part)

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2024-10-11 pull for surprise
2024-10-25 surprises
2024-10-31 Add files via upload
    Thonny pico to ground station
2024-11-08 Revert "k"
    This reverts commit 38966a600e7b2a088c3d6b0a2184c3d74b49fc93.
2024-11-10 file management
2024-11-10 uart test files
2024-11-12 Create Ground Station
2024-11-15 ascdasd
2024-11-16 working uartread!!!
2024-11-16 i squirted on the repo!!!
2024-11-21 Update GRITSGroundStation
2025-01-08 telegps files
2025-02-06 Add files via upload
    Beware written by AI - supposed to read from the RRC3 and write a packet to flash
2025-02-22 added IMU stuff
2025-03-01 AAAAAAAAAAAAAAAAA
    :( :( :( :( :( hnuiobfew
2025-04-06 struct example code
2025-04-15 Added initial data analysis scripts and additional spreadsheets
2025-04-15 telegps eeprom
2025-04-16 Added additional features
2025-04-23 another update
2025-04-27 my first commit ever <3
2025-04-27 it dont work
2025-04-30 I think I'm done
2025-05-02 i cant believe you dont have github desktop OR git bash installed
2025-05-03 final ground station
2025-05-03 airbrakes test code
2025-05-03 actual final airbrakes test code
2025-05-03 killing myself
2025-05-12 organize
2025-05-26 heyy
2025-05-26 i actually dont know whats going on
2025-06-22 old stuff
2025-06-22 Converted telemtery to CSV
2025-06-23 Oops I forgot to dump the data
2025-09-12 added schematic
2025-09-12 hi
    ohello!
2025-09-13 Test Project
    Created Project to learn KiCad (KiCad sucks)
2025-09-15 testing kicad
2025-09-15 dont need the backups smh
2025-09-15 :D pcb done
2025-09-15 gerb
2025-09-17 Created EGSE Proj
2025-09-18 Kicad is my hell
2025-09-25 Added initial RocketPy Cloud Test
2025-09-25 STM Schematic
    Created schematic with preliminary STMs
2025-09-26 Made schematic Hierarchical
2025-09-28 SD Card Routed
2025-09-28 Added Ferite Bead
2025-09-29 Battery Charge Schematic Done
2025-09-29 Okay KICAD isn't so bad
2025-09-29 I'm Tired
2025-09-29 goof
2025-09-29 67 ha ha ha ha ha
2025-09-30 2016 Cavs Finals
2025-10-02 work on power stuff
    yuh
2025-10-02 Fixed Ferrite bead and SD card
2025-10-03 ralnodm
2025-10-03 added stuff to 6 7 ha ha ha ha ha
2025-10-03 Added DeMultiplexer
2025-10-04 Finished SWD Connector
2025-10-05 label making and imported protection footprint
2025-10-05 put footprint
2025-10-05 include foot
2025-10-05 I'm Hungry (Added Camera Connectors)
2025-10-06 here comes the
2025-10-06 Connected DCMI
2025-10-06 hiiiiiiiii!!!!!!!!
2025-10-06 heeeloooooooooooo
2025-10-06 oops i delieted everything
2025-10-06 uhhhhh
2025-10-07 Added Pulldown R
2025-10-08 SOMEONE CHECK MY SHIT !!!!!!!!!
    TITLE!!!!!!!!!!!!
2025-10-08 connecting 6 or 7 wires ha ha ha ha ha ha ha
2025-10-08 doing sensors ha ha
2025-10-08 SENSORS WIRED RAHHHHHHHHHHHHHHHHH
2025-10-08 added labels for clarity
2025-10-09 Tried to do stuff
    (Added I2C Buffer and Level shifter)
2025-10-12 Added RunCam stuff
2025-10-13 LDO SPAM
2025-10-13 ground
2025-10-13 shaboining
2025-10-13 slumpt
2025-10-13 Added Multiplexer
2025-10-13 Forgot something
2025-10-13 done
2025-10-13 Fixing small error
2025-10-13 Added Flash IC
2025-10-13 DRU file
2025-10-13 added more copper on pwr path
2025-10-14 stuff
2025-10-14 gpio
2025-10-15 Fixed Multiplexer
2025-10-15 beep beep beep placed
2025-10-15 Small edits
2025-10-16 Trying to figure out Transceiver
2025-10-16 monitoring
2025-10-16 things... and stuff
2025-10-16 strange...
2025-10-16 deleteeeeeeeeee
2025-10-17 helloooo
2025-10-17 TRANSWHATEVER
2025-10-17 Header or something
2025-10-17 power
2025-10-18 PWM Connector
2025-10-21 sx1281 + initial front end
2025-10-22 ts updates for ts sx1281
2025-10-22 buck
2025-10-23 radio development
2025-10-23 Can't change I2S
2025-10-26 50 changed files 💀
2025-10-26 more
2025-10-26 AAAAAAAAAA
2025-10-26 chud
2025-10-27 Adding Footprints
2025-10-28 Added most footprints
2025-10-29 Can start Routing
2025-10-29 added antena
2025-11-03 Started Routing Camera stuff
2025-11-03 hi!!!!!
2025-11-03 special commit
2025-11-03 hello
2025-11-03 Revert "hello"
    This reverts commit 5e0c8077565b0059be07f7c50d566ef924147ec7.
2025-11-03 i fix
2025-11-03 started pcb design
2025-11-04 Tried to route DCMI and started SWD connector
2025-11-05 pcb started igggggggg
2025-11-08 NTSR routed (Bad but routed)
2025-11-09 Figured out STM Placement
2025-11-09 0805
2025-11-10 Made shit the same length
2025-11-10 hello twin backup + commits
2025-11-10 Revert "bru"
    This reverts commit 61923852d4babe58a7a08e3d1d05d8dbb76b1459.
2025-11-10 uhhhh didnt do as much as i shoulve mb gang
2025-11-10 antenna done😭🙏
2025-11-10 i hope this does not explode anything
    ya
2025-11-10 Revert "Merge branch 'main' of https://github.com/parsa-novin/UGA-IREC"
    This reverts commit e2959594469ec66c817ca262014a8b4f6b7feb7a, reversing
    changes made to fdf15d52d17582f47c705e24bcf8ee865dfea6d9.
2025-11-10 Revert "i hope this does not explode anything"
    This reverts commit fdf15d52d17582f47c705e24bcf8ee865dfea6d9.
2025-11-10 oh fuck
2025-11-10 oh fuck1
2025-11-10 idfk
    Revert "i hope this does not explode anything"
    This reverts commit fdf15d52d17582f47c705e24bcf8ee865dfea6d9.
    Revert "Merge branch 'main' of https://github.com/parsa-novin/UGA-IREC"
    This reverts commit e2959594469ec66c817ca262014a8b4f6b7feb7a, reversing
    changes made to fdf15d52d17582f47c705e24bcf8ee865dfea6d9.
2025-11-10 Revert "idfk"
    This reverts commit 0070fecce818f813fe9229ed31d16c769b6f3c34.
2025-11-10 Reapply "idfk"
    This reverts commit 94ab89a68d5018b92cacbc7352bf51d23d88c6b5.
2025-11-10 plz work
2025-11-10 hello twin
2025-11-10 sigh
2025-11-10 uhhhhhhh i uploaded an old save? srry if i messed smth up
2025-11-11 yay done
2025-11-11 oopsies
2025-11-11 Crazy Routing
    James get your work done!!!!
2025-11-13 STM SWD wired
2025-11-14 Stated Cam to STM
2025-11-14 maybe
2025-11-15 doing some routinggggg
2025-11-15 organizing some things ig
2025-11-16 Did stuff
2025-11-17 updated some labels idk
2025-11-17 fix j2 header
2025-11-17 oops
2025-11-17 changed a lableeeeee
2025-11-17 Trolling
2025-11-17 uhhhh its not working agian
2025-11-17 oh wow
2025-11-18 Level Shifter and Fixing errors
2025-11-18 uhhhhhh theres a lot of vias oh well
2025-11-19 STM routing
2025-11-21 Moved Trasciever
2025-11-22 Created Satnogs GS
2025-11-22 dfdf
2025-11-22 Finished almost
2025-11-22 uhhh idk i got the same color wires over each other for fun ig
2025-11-25 bruh
2025-11-30 Fixed everything on my side
    RX TX Stuff
    Db15 Pinout
    Impedance matching and differential pair for rs-422
2025-12-01 uhhhhhhhh idk
2025-12-01 grrrr
2025-12-01 its over
2025-12-01 shmovwe
2025-12-02 i sitll got mroe to do ssry yall
2025-12-02 fixed unconnected ground (singular i thought it was more)
2025-12-02 were almost there i swear im just spleeyp
2025-12-03 uhhhhhh i think its almost done now?
2025-12-05 holy
2025-12-05 waaa
2025-12-06 not important changes
2026-01-26 cooked
2026-01-26 csvs i think
2026-02-12 ENIAC.drawio
2026-02-12 Added ENIAC.drawio
2026-02-16 blow up the repo i am ted kaczynski
2026-02-16 errrrrrr i forgot to do my task srry yall
2026-02-23 Started C6v1, Got STM most set up
2026-02-23 Updated IO on shi
2026-02-24 FK TS PMO GGKMSRQTOGIW
2026-02-24 merge
2026-02-24 more merge
2026-02-24 uhhh idk
2026-02-25 fixing
2026-02-25 delete
2026-02-25 i finally finished routing everything to spi
2026-02-25 uhhhh im confused gang
2026-02-26 commit gng gng
2026-02-26 yikes
2026-02-27 pingus
2026-02-28 made voltage sense more accurate to 1%
2026-03-02 foot!
2026-03-02 gooning
2026-03-02 push
2026-03-02 save
2026-03-02 EGSE2 arisen
2026-03-02 gnding
2026-03-02 im scared
2026-03-02 I think the schematics done uhhh idrk
2026-03-03 DCMI1-Me0
2026-03-03 im sorry parsa :/
2026-03-04 john d tickle
2026-03-04 sasha sneaky academic
2026-03-04 not albino tiger shark
2026-03-06 errrrrr i cant find a umcx connector they all say there like $50??
2026-03-07 i have no idea whats going on, everything crashed and nothing will open
2026-03-07 idk whats going on anymore
2026-03-09 gamig on this EGSE type hsi
2026-03-09 funny commit message
2026-03-09 fix rocketpy in main
2026-03-10 sneaky commit
2026-03-12 finaly
2026-03-12 made RS-422 120 impedance
2026-03-12 netclasses SUCK
2026-03-12 PEAK PLL ROUTING
2026-03-13 changed the inductor sizing
2026-03-13 finally............
2026-03-13 sneaky on/off
2026-03-13 via hole
2026-03-17 i hate sims
2026-03-19 small changes
2026-03-31 holy hell
2026-04-07 urethra!
2026-04-10 ground station v1
2026-04-11 holy antiquated
2026-04-11 mega
2026-04-28 the fish in the amazon that can swim up your pee stream into your urethra
2026-04-29 feedback
2026-05-19 kjkkj
2026-05-24 im quitting irec
